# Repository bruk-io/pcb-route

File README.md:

# pcb-route

A fast autorouter for KiCad boards that, above all, reroutes incrementally: given the previous
route, it keeps what an edit left standing and routes again only what the edit disturbed. Nothing
is locked except hand-laid copper. It reads a Specctra design and writes a Specctra session, on
Freerouting's command line (`-de board.dsn -do board.ses -mp 40`), so it can run where Freerouting
is called today.

On the one real board it has been measured on (a two-layer robot carrier, below), a full route
takes 55 s against Freerouting's 337 s, and rerouting after a small edit takes 3.5 s, both clean
under KiCad's DRC. It uses more vias than Freerouting (98 against 58). Freerouting can also keep
existing copper, routing only what is missing; that mode has not been timed against this one yet.

## Use

```
python route.py -de kicad/board.dsn -do kicad/board.ses -mp 40 --board kicad/prerouted.kicad_pcb
python route.py ... --previous golden/board.ses        # incremental; golden/prerouted.kicad_pcb is read too
```

| Flag | Meaning |
| --- | --- |
| `-de`, `-do`, `-mp` | As Freerouting: design in, session out, most negotiation rounds |
| `--board` | The KiCad board the DSN was written from (geometry and rules come from it) |
| `--previous` | A previous session of this board, to reuse |
| `--previous-board` | The board that session was routed on (default: `prerouted.kicad_pcb` beside it) |
| `--max-seconds` | No new round after this; the result so far is written (default 600) |
| `--min-width` | No track narrower than this, in mm |
| `--seed` | A different net order and starting prices, for a retry |
| `--via-cost` | Millimetres of track one via is worth in the finished route (default 16); raise it for fewer vias, at more time. Negotiation settles with cheap vias first (2.4 mm, or `--via-cost` if lower); via passes then reroute the nets that have vias at this cost |
| `--cache` | Where board exports are kept (default `~/.cache/pcb-route`, or `PCB_ROUTE_CACHE`) |

Log lines match Freerouting's: `Starting auto-routing...`, `Auto-routing was completed in N seconds.`,
`Saving '<file>'...`, plus `Router: <rounds> rounds, <vias> vias, <cells> cells searched`. SIGTERM
finishes the net being routed and writes the result (a via pass under way is dropped). Exit code 0
when every net is routed without conflict, 2 when something is left, 1 when nothing was written.

Pads wholly inside a track keep-out (under a pour) are left for the pour, as Freerouting leaves them;
the log lists them.

### Install

Needs KiCad 10's Python (`pcbnew`; set `KICAD_PYTHON` if it is not `/usr/bin/python3`), numpy,
matplotlib, and the router built with Mojo 1.1 (`pip install mojo`):

```
mojo build -D ASSERT=none -o router/negotiate router/negotiate.mojo
```

`-D ASSERT=none` turns off Mojo's bounds check on every collection index, which costs the router a
fair share of its speed. Mojo runs on Linux and macOS (on Windows, through WSL).

### Tests

`python -m pytest tests` (about 6 minutes). The quick tests route pcbkit's blinky example, from a
pcbkit checkout beside this repository (or set `PCBKIT`); the rest use the robot carrier in
`boards/spot`. `tests/test_snapshots.py` pins the router's output; a change that alters it fails
until accepted with `UPDATE_SNAPSHOTS=1` (the test's docstring says when that is right).

## How it works

1. `board.py` turns the KiCad board into a grid (0.05 mm cells per layer): for each net class,
   which net may stand in each cell, where it may drill, and each net's pads. Exports are cached;
   after an edit, the edited board is read as a patch of the previous export, redrawing only the
   grid around what changed, with the same result as a full read (`tests/test_patch.py`).
2. With `--previous`, `incremental.py` works out which pieces of the previous route still stand on
   the edited grid; they are offered to the router as kept copper.
3. The router (`router/`) routes every net with A* on the grid, then negotiates: cells two nets
   share get dearer every round, and the nets in conflict are routed again, until none share a
   cell. Kept copper is laid first and is only routed afresh if other nets keep running over it.
4. Via passes: once the board has settled with cheap vias, vias get dearer, the nets that have
   them are routed again, and negotiation settles the board again. If it does not, or vias do not
   fall, the earlier result stands.
5. Tidying: a grid path alternates straight and diagonal steps. Each connection is redrawn between
   its fixed points (ends, vias, junctions) as runs of at most two pieces, one straight and one
   at 45 degrees, wherever every cell of the run is clear of other copper.
6. `ses.py` writes the session; reused pieces are written as they were.

## Results on the robot carrier (12 Oct 2026, one 2-core cloud machine)

The board: a 127 x 95 mm two-layer carrier with about 160 parts. The edit: C2, C41, C50 and C51
moved (`boards/spot/golden` to `boards/spot/kicad`). Each session was imported into pcbnew 10 and
checked with KiCad DRC at every severity, before pours.

| Run | Wall time | Copper problems | Vias | Track pieces | Track |
| --- | --- | --- | --- | --- | --- |
| Freerouting 1.9.0, `-mp 40`, full route | 337 s | 4 unconnected (3 connections at U8 left unrouted) | 58 | 1,453 | 4,490 mm |
| pcb-route, full route, cold cache | 55 s (43 s routing) | 0 | 98 | 1,588 | 3,961 mm |
| pcb-route, full route, `--via-cost 2.4` (no via passes), board export cached | 17 s | 0 | 169 | 1,520 | 3,612 mm |
| pcb-route, full route, `--via-cost 40`, board export cached | 91 s | 0 | 71 | 1,720 | 4,366 mm |
| pcb-route, `--previous golden/...`, golden export cached | 3.5 s | 0 | 75 | 1,559 | 4,791 mm |

The incremental run keeps 96% of the previous route's track; the edited board is read as a patch
in 1.6 s. Of the full route's 98 vias, about 17 are on the three U8 connections Freerouting left
unrouted. No router via lands in a surface-mount pad or within the board's hole-to-hole distance
of an existing hole; hand-laid tracks and vias are untouched (they are not written to the session).

## Known limits

* Measured on one real board and one small example. Dense 4- to 6-layer boards and fine-pitch
  BGAs are untried.
* More vias than Freerouting. Most of the rest are crossings: a track meets another net's track
  on its layer, and no detour cheaper than the via cost is clear.
* No length matching, differential pairs or impedance control.
* `--min-width` above the net classes' own widths widens every track; on the carrier that left two
  fine-pitch pads unreachable and 3 clearance faults. At or below the class widths it is only a
  floor.
* Reused copper is trusted where the edit did not change what may stand in its cells; a net whose
  class width or clearance changed is routed afresh.
* The time limit and SIGTERM stop after the net being routed; a SIGTERM before routing starts
  (while the board is read) leaves no session.
* The grid takes memory: about 190 MB per export of the carrier, and about 0.7 GB while routing.

## Use from pcbkit

This began as the router for pcbkit, a board-as-code tool (`INTENT.md` has the
problem it set out to solve). There:

* `build_command`: the command line above, `--board` = the board `pre` wrote the DSN from.
* `pcbkit route --eco`: pass `--previous golden/<stem>.ses` instead of copying and locking copper.
* The retry loop: pass `--seed <try number>`; results are otherwise deterministic.

## Files

* `route.py` - the command line
* `board.py` - KiCad 10 board to the router's grid (pre-routes, keep-outs, per-pad clearances)
* `incremental.py` - which of the previous session's pieces still stand
* `router/` - the router: `negotiate.mojo` the command line, negotiation and via passes,
  `board.mojo` the grid and nets, `congestion.mojo` prices and footprints, `search.mojo` the A*
  search, `tidy.mojo` the straightening, `cost.mojo` step costs, `buffer.mojo` lazily zeroed
  per-cell storage, `stop.mojo` SIGTERM, `mt19937.mojo` the seeded jitter
* `ses.py` - the session writer
* `check.py` - import a session with pcbnew and count KiCad DRC's copper problems
* `tests/test_route.py` - the command line's contract
* `tests/test_patch.py` - a patched board read equals a full read, for each kind of edit
* `tests/test_snapshots.py` - the router's output, pinned
* `tests/test_quality.py` - tidying and via passes keep the route conflict-free, and full and
  incremental routes pass KiCad DRC

## How the router got fast (12 Oct 2026, robot carrier)

The router began as a C++ program. Its first Mojo version was a straight port that matched it byte
for byte at the same speed (a full route in 47 s against 48 s); the changes below, each measured on
its own with the output compared every time, then halved that, before via passes and tidying were
added:

* Pricing a via site (the dearest cell under the via, on every layer) was over half a full route.
  Each row of the via's disc is scanned in SIMD vectors, and where no copper covers a vector, a
  cell's price is exactly `1 + history`, so only the largest history is needed.
* A via is priced only when its turn comes in the search: it is queued at the cheapest a via can
  be, and most queued vias never come up. The paths found are as cheap; the search takes 30% less
  time, and about 40% less in a via pass.
* The A* estimate divided twice per neighbour to find its row and column; neighbours take them
  from the cell being expanded, and the one division left per expansion is 32-bit unsigned.
* A cell's best cost, "seen" and "closed" marks sit in one 16-byte record, so a visit reads one
  cache line, not three.
* Counting a net's keep-out footprint was 40% of an incremental run. Rows are tested 16 cells at
  a time and only unmarked cells are visited; when a path cell is next to the one before it, only
  the edge of the disc that the step uncovers can hold unmarked cells.
* Page faults were a third of an incremental run's time. Grid-sized buffers are mapped with huge
  pages (Linux), and the board's grids are read straight into them: 200k faults down to 15k.

Where the time goes as `--via-cost` rises: the search, not the arithmetic. Once a track is blocked
on its layer, A* has to try every detour cheaper than a via before it takes one, so the cells
searched grow with about the square of the via cost (79 M cells at 2.4 mm, 221 M at 16 mm, 520 M
at 40 mm), at about 190 ns each. On the default full route: negotiation 17 s, the first via pass
20 s, the second 4 s, tidying under 1 s. Charging the higher via cost through every negotiation
round instead of in via passes costs 2-5 times the time for the same vias.

Tried and dropped: packing occupancy, kept copper and history into one record per class (no
faster); skipping a via's price when every other layer is already reached more cheaply (under 0.1%
of sites); counting the via a cell's layer forces into the A* estimate (target pads are rarely on
one layer only); restarting the sharing price for a via pass (never settled); taking vias out
while tidying through clear cells only (8 vias for 4 s; a via pass does better).

Notes on Mojo 1.1: `List.read_bytes()` took 0.45 s on the 200 MB board file against 0.17 s for C's
`fread`, so grids are read into buffers directly. The Mojo runtime runs threads of its own, so
blocking SIGTERM on the main thread is not enough: a C-ABI handler passes a stop signal on to the
main thread, which polls for it between nets. An environment variable set to an empty value counts
as unset, and numbers must parse cleanly.

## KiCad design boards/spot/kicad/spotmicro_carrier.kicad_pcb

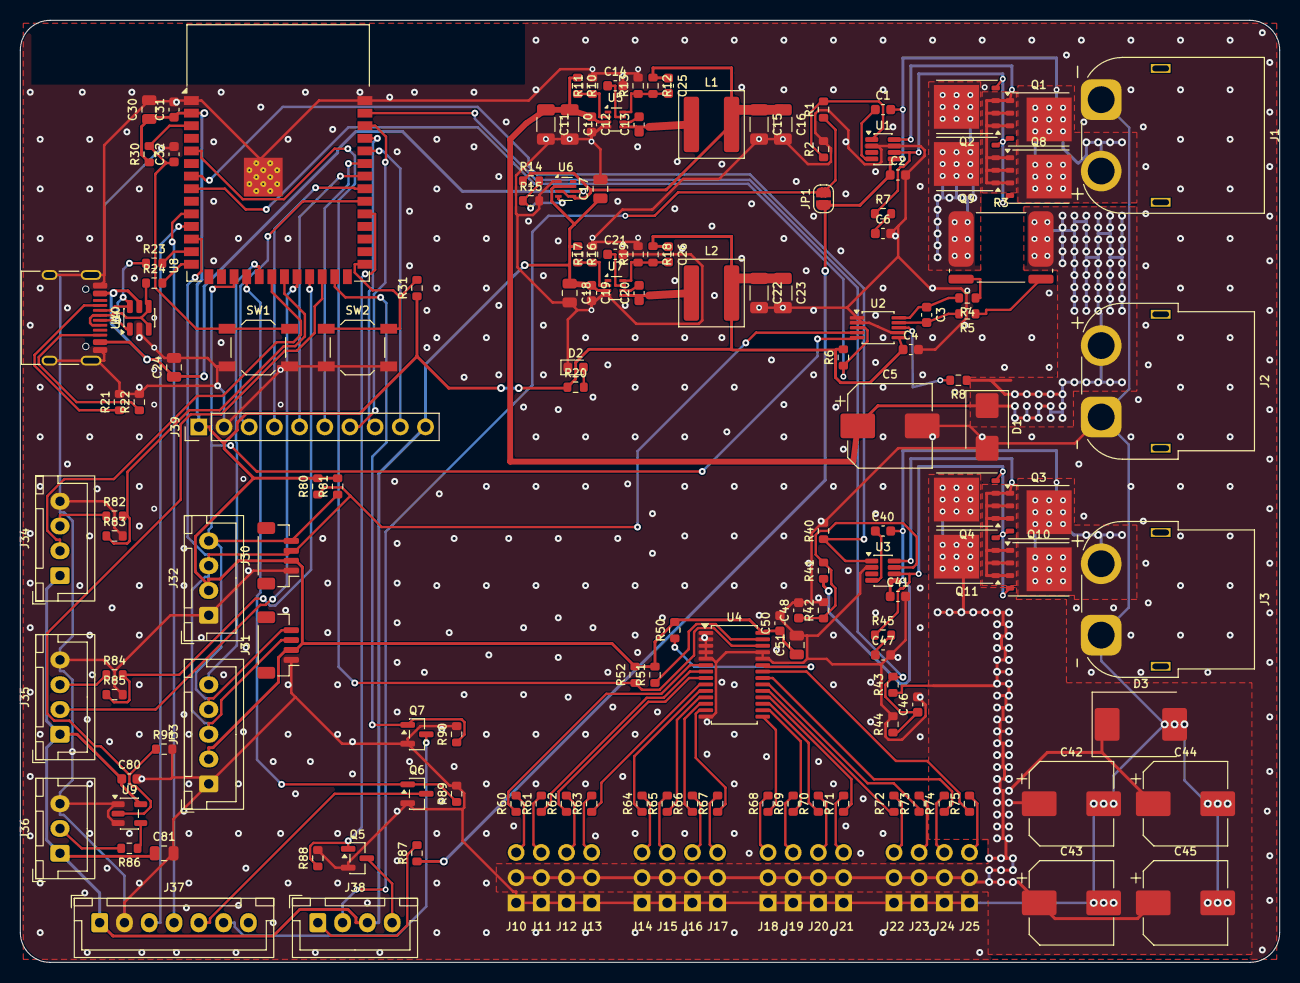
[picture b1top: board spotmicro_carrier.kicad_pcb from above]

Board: 2 copper layers, 127.0 x 95.0 mm, 160 parts (0 on the bottom side), 113 nets.

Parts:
C1, C40: 470n; C_0603_1608Metric
C2, C3, C4, C6, C12, C13, C19, C20, C31, C41, C46, C47, C48, C50, C80: 100n; C_0603_1608Metric
C5, C42, C43, C44, C45: 470u 16V; CP_Elec_8x10
C10, C11: 10u; C_1206_3216Metric
C14, C21: 33n; C_0603_1608Metric
C15, C16, C22, C23: 22u; C_1206_3216Metric
C17, C30: 22u; C_0805_2012Metric
C18, C24, C51, C81: 10u; C_0805_2012Metric
C25, C26: 220p; C_0603_1608Metric
C32: 1u; C_0603_1608Metric
D1: SMBJ8.5A; D_SMB
D2: Green; LED_0603_1608Metric
D3: SMCJ7.0A; D_SMC
J1: BATTERY 2S; AMASS_XT60PW-M_1x02_P7.20mm_Horizontal
J2: TO SERVO BUCK; AMASS_XT60PW-F_1x02_P7.20mm_Horizontal
J3: FROM SERVO BUCK; AMASS_XT60PW-F_1x02_P7.20mm_Horizontal
J4: USB-C; USB_C_Receptacle_HRO_TYPE-C-31-M-12
J10: CH0 FLS; PinHeader_1x03_P2.54mm_Vertical_Servo
J11: CH1 FLU; PinHeader_1x03_P2.54mm_Vertical_Servo
J12: CH2 FLL; PinHeader_1x03_P2.54mm_Vertical_Servo
J13: CH3 FRS; PinHeader_1x03_P2.54mm_Vertical_Servo
J14: CH4 FRU; PinHeader_1x03_P2.54mm_Vertical_Servo
J15: CH5 FRL; PinHeader_1x03_P2.54mm_Vertical_Servo
J16: CH6 RLS; PinHeader_1x03_P2.54mm_Vertical_Servo
J17: CH7 RLU; PinHeader_1x03_P2.54mm_Vertical_Servo
J18: CH8 RLL; PinHeader_1x03_P2.54mm_Vertical_Servo
J19: CH9 RRS; PinHeader_1x03_P2.54mm_Vertical_Servo
J20: CH10 RRU; PinHeader_1x03_P2.54mm_Vertical_Servo
J21: CH11 RRL; PinHeader_1x03_P2.54mm_Vertical_Servo
J22: CH12 AUX12; PinHeader_1x03_P2.54mm_Vertical_Servo
J23: CH13 AUX13; PinHeader_1x03_P2.54mm_Vertical_Servo
J24: CH14 AUX14; PinHeader_1x03_P2.54mm_Vertical_Servo
J25: CH15 AUX15; PinHeader_1x03_P2.54mm_Vertical_Servo
J30, J31: QWIIC; JST_SH_BM04B-SRSS-TB_1x04-1MP_P1.00mm_Vertical
J32: OLED; JST_XH_B4B-XH-A_1x04_P2.50mm_Vertical
J33: IMU; JST_XH_B5B-XH-A_1x05_P2.50mm_Vertical
J34: SONAR L; JST_XH_B4B-XH-A_1x04_P2.50mm_Vertical
J35: SONAR R; JST_XH_B4B-XH-A_1x04_P2.50mm_Vertical
J36: LED RING; JST_XH_B3B-XH-A_1x03_P2.50mm_Vertical
J37: ESP32-CAM; JST_XH_B7B-XH-A_1x07_P2.50mm_Vertical
J38: POWER BTN; JST_XH_B4B-XH-A_1x04_P2.50mm_Vertical
J39: EXPANSION; PinHeader_1x10_P2.54mm_Vertical
JP1: ALWAYS ON; SolderJumper-2_P1.3mm_Open_RoundedPad1.0x1.5mm
L1: 6.8u; L_Bourns_SRP6060FA
L2: 4.7u; L_Bourns_SRP6060FA
Q1, Q2, Q3, Q4, Q8, Q9, Q10, Q11: BSC010N04LS; TDSON-8-1
Q5, Q6, Q7: 2N7002; SOT-23
R1: 38.3k; R_0603_1608Metric
R2, R6, R13, R15, R19, R30, R31, R42, R44, R50, R82, R84, R91: 10k; R_0603_1608Metric
R3: 1m; R_Shunt_Isabellenhuette_BVR4026
R4, R5: 10; R_0603_1608Metric
R7, R8, R45: 100; R_0603_1608Metric
R10, R16, R17, R40, R88, R89, R90: 100k; R_0603_1608Metric
R11, R43: 47k; R_0603_1608Metric
R12: 52.3k; R_0603_1608Metric
R14: 35.7k; R_0603_1608Metric
R18: 31.6k; R_0603_1608Metric
R20, R87: 1k; R_0603_1608Metric
R21, R22: 5.1k; R_0603_1608Metric
R23, R24: 22; R_0603_1608Metric
R41: 49.9k; R_0603_1608Metric
R51, R52, R80, R81: 2.2k; R_0603_1608Metric
R60, R61, R62, R63, R64, R65, R66, R67, R68, R69, R70, R71, R72, R73, R74, R75: 220; R_0603_1608Metric
R83, R85: 15k; R_0603_1608Metric
R86: 330; R_0603_1608Metric
SW1: RESET; SW_SPST_TL3342
SW2: BOOT; SW_SPST_TL3342
U1, U3: LM74502-Q1; SOT-23-8
U2: INA226; MSOP-10_3x3mm_P0.5mm
U4: PCA9685PW; TSSOP-28_4.4x9.7mm_P0.65mm
U5, U7: TPS62933; SOT-583-8
U6: TPS2116; SOT-583-8
U8: ESP32-S3-WROOM-1-N8R2; ESP32-S3-WROOM-1
U9: 74AHCT1G125; SOT-23-5
U10: USBLC6-2SC6; SOT-23-6

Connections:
/+3V3: C4.1, C22.1, C23.1, C26.1, C30.1, C31.1, C50.1, C51.1, J30.2, J31.2, J32.2, J33.2, J39.1, L2.2, R6.2, R18.1, R20.1, R30.1, R31.1, R50.2, R51.2, R52.2, R80.2, R81.2, U2.6, U4.28, U8.2
/+5V: C17.1, C18.1, C19.1, C80.1, C81.1, J34.1, J35.1, J36.1, J37.1, J38.3, J39.10, R16.1, U6.2, U6.7, U7.3, U9.5
/+5V_BUCK: C15.1, C16.1, C25.1, L1.2, R12.1, R14.1, U6.3, U6.5
/BAT_DVDT: C6.1, R7.2
/BAT_EN: R1.2, R2.1, U1.1
/BAT_GATE: Q1.4, Q2.4, Q8.4, Q9.4, R7.1, U1.6
/BAT_SRC: Q1.1, Q1.2, Q1.3, Q2.1, Q2.2, Q2.3, Q8.1, Q8.2, Q8.3, Q9.1, Q9.2, Q9.3, U1.8
/BAT_VCAP: C1.1, U1.4
/BOOT: R31.2, SW2.1, U8.27
/BTN_C: J38.1, R87.2
/BTN_LED: Q5.1, R88.1, U8.31
/BTN_LED_K: J38.4, Q5.3
/BTN_NO: J38.2, JP1.2, R1.1
/BUCK3_BST: C20.2, U7.6
/BUCK3_EN: R16.2, R17.1, U7.2
/BUCK3_FB: C26.2, R18.2, R19.1, U7.8
/BUCK3_SS: C21.1, U7.7
/BUCK3_SW: C20.1, L2.1, U7.5
/BUCK5_BST: C13.2, U5.6
/BUCK5_EN: R10.2, R11.1, U5.2
/BUCK5_FB: C25.2, R12.2, R13.1, U5.8
/BUCK5_SS: C14.1, U5.7
/BUCK5_SW: C13.1, L1.1, U5.5
/CAM_BOOT: Q6.1, R89.1, U8.18
/CAM_EN: J37.6, Q7.3
/CAM_INT: J37.7, U8.9
/CAM_IO0: J37.5, Q6.3
/CAM_RST: Q7.1, R90.1, U8.25
/CAM_RX: J37.4, U8.10
/CAM_TX: J37.3, U8.11
/ESP_DN: R23.2, U8.13
/ESP_DP: R24.2, U8.14
/ESP_EN: C32.1, R30.2, SW1.1, U8.3
/EXP_IO2: J39.7, U8.38
/EXP_IO39: J39.3, U8.32
/EXP_IO40: J39.4, U8.33
/EXP_IO41: J39.5, U8.34
/EXP_IO42: J39.6, U8.35
/EXP_RXD0: J39.9, U8.36
/EXP_TXD0: J39.8, U8.37
/GND: C2.2, C4.2, C5.2, C6.2, C10.2, C11.2, C12.2, C14.2, C15.2, C16.2, C17.2, C18.2, C19.2, C21.2, C22.2, C23.2, C24.2, C30.2, C31.2, C32.2, C41.2, C42.2, C43.2, C44.2, C45.2, C46.2, C47.2, C48.2, C50.2, C51.2, C80.2, C81.2, D1.2, D2.1, D3.2, J1.1, J2.1, J3.1, J4.A1, J4.A12, J4.B1, J4.B12, J4.SH, J10.1, J11.1, J12.1, J13.1, J14.1, J15.1, J16.1, J17.1, J18.1, J19.1, J20.1, J21.1, J22.1, J23.1, J24.1, J25.1, J30.1, J31.1, J32.1, J33.1, J34.4, J35.4, J36.3, J37.2, J39.2, Q5.2, Q6.2, Q7.2, R2.2, R11.2, R13.2, R15.2, R17.2, R19.2, R21.2, R22.2, R40.2, R42.2, R44.2, R83.2, R85.2, R88.2, R89.2, R90.2, R91.2, SW1.2, SW2.2, U1.2, U1.7, U2.1, U2.2, U2.7, U3.2, U4.1, U4.2, U4.3, U4.4, U4.5, U4.14, U4.24, U4.25, U5.4, U6.1, U7.4, U8.1, U8.40, U8.41, U9.1, U9.3, U10.2
/IMU_INT: J33.5, U8.19
/INA_ALERT: R6.1, U2.3, U8.8
/INA_INN: C3.2, R5.2, U2.9
/INA_INP: C3.1, R4.2, U2.10
/INA_VBUS: R8.2, U2.8
/LED_DATA: J36.2, R86.2
/LED_DATA_3V3: R91.1, U8.24, U9.2
/LED_DATA_BUF: R86.1, U9.4
/MUX_PR1: R14.2, R15.1, U6.4
/PCA_OE: R50.1, U4.23, U8.6
/PWM0: R60.1, U4.6
/PWM1: R61.1, U4.7
/PWM2: R62.1, U4.8
/PWM3: R63.1, U4.9
/PWM4: R64.1, U4.10
/PWM5: R65.1, U4.11
/PWM6: R66.1, U4.12
/PWM7: R67.1, U4.13
/PWM8: R68.1, U4.15
/PWM9: R69.1, U4.16
/PWM10: R70.1, U4.17
/PWM11: R71.1, U4.18
/PWM12: R72.1, U4.19
/PWM13: R73.1, U4.20
/PWM14: R74.1, U4.21
/PWM15: R75.1, U4.22
/PWR_LED: D2.2, R20.2
/P_SCL: J30.4, J31.4, J32.4, J33.4, R81.1, U2.5, U8.17
/P_SDA: J30.3, J31.3, J32.3, J33.3, R80.1, U2.4, U8.12
/SERVO_EN: R40.1, U3.1, U8.7
/SHUNT_N: R3.3, R5.1
/SHUNT_P: R3.2, R4.1
/SRV0: J10.3, R60.2
/SRV1: J11.3, R61.2
/SRV2: J12.3, R62.2
/SRV3: J13.3, R63.2
/SRV4: J14.3, R64.2
/SRV5: J15.3, R65.2
/SRV6: J16.3, R66.2
/SRV7: J17.3, R67.2
/SRV8: J18.3, R68.2
/SRV9: J19.3, R69.2
/SRV10: J20.3, R70.2
/SRV11: J21.3, R71.2
/SRV12: J22.3, R72.2
/SRV13: J23.3, R73.2
/SRV14: J24.3, R74.2
/SRV15: J25.3, R75.2
/SRV_DVDT: C47.1, R45.2
/SRV_GATE: Q3.4, Q4.4, Q10.4, Q11.4, R45.1, U3.6
/SRV_OV: C48.1, R41.2, R42.1, U3.7
/SRV_SRC: Q3.1, Q3.2, Q3.3, Q4.1, Q4.2, Q4.3, Q10.1, Q10.2, Q10.3, Q11.1, Q11.2, Q11.3, U3.8
/SRV_VCAP: C40.1, U3.4
/S_SCL: R52.1, U4.26, U8.5
/S_SDA: R51.1, U4.27, U8.4
/USB_CC1: J4.A5, R21.1
/USB_CC2: J4.B5, R22.1
/USB_DN: J4.A7, J4.B7, R23.1, U10.1, U10.6
/USB_DP: J4.A6, J4.B6, R24.1, U10.3, U10.4
/USL_ECHO: R82.2, R83.1, U8.21
/USL_ECHO5: J34.3, R82.1
/USL_TRIG: J34.2, U8.20
/USR_ECHO: R84.2, R85.1, U8.23
/USR_ECHO5: J35.3, R84.1
/USR_TRIG: J35.2, U8.22
/VBAT: C5.1, C10.1, C11.1, C12.1, D1.1, J2.2, R3.4, R8.1, R10.1, U5.3
/VBAT_RAW: C1.2, C2.1, J1.2, JP1.1, Q1.5, Q8.5, R87.1, U1.5
/VBAT_SW: Q2.5, Q9.5, R3.1
/VBUS: C24.1, J4.A4, J4.A9, J4.B4, J4.B9, U6.6, U10.5
/VSERVO: C42.1, C43.1, C44.1, C45.1, D3.1, J10.2, J11.2, J12.2, J13.2, J14.2, J15.2, J16.2, J17.2, J18.2, J19.2, J20.2, J21.2, J22.2, J23.2, J24.2, J25.2, Q4.5, Q11.5, R43.1
/VSERVO_IN: C40.2, C41.1, J3.2, Q3.5, Q10.5, R41.1, U3.5
/VSERVO_SENSE: C46.1, R43.2, R44.1, U8.39
